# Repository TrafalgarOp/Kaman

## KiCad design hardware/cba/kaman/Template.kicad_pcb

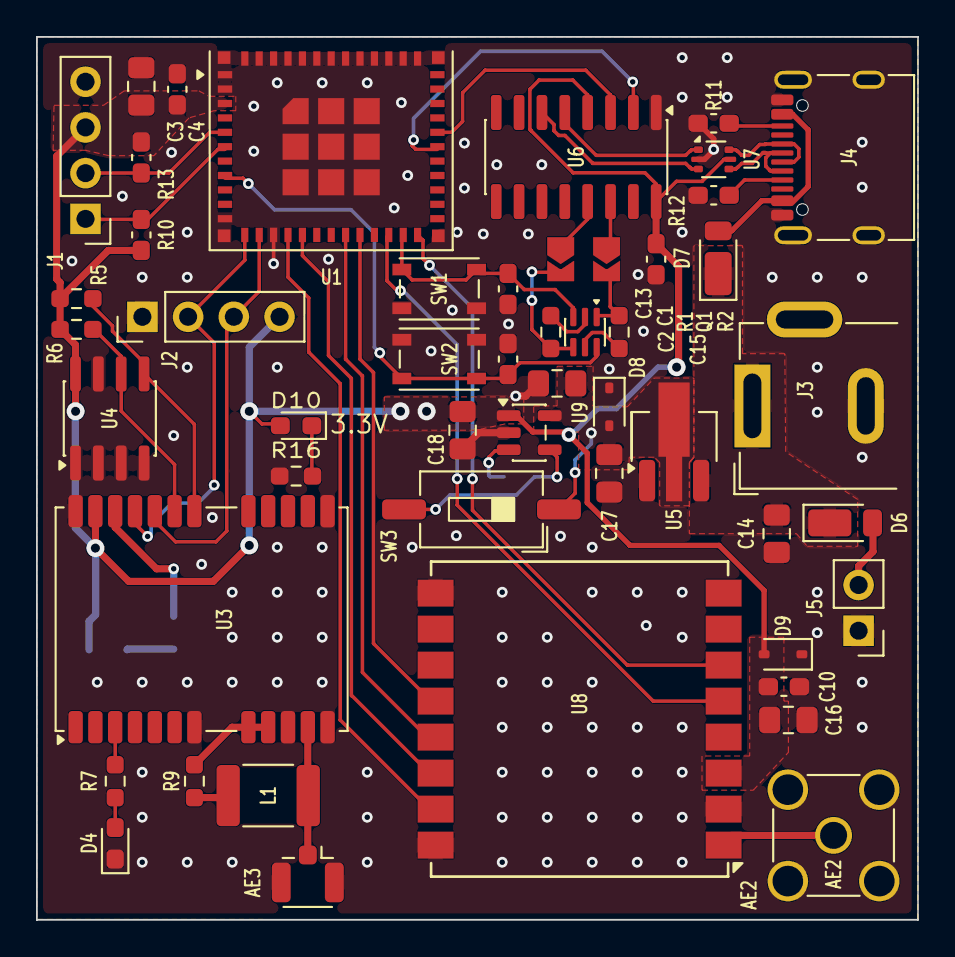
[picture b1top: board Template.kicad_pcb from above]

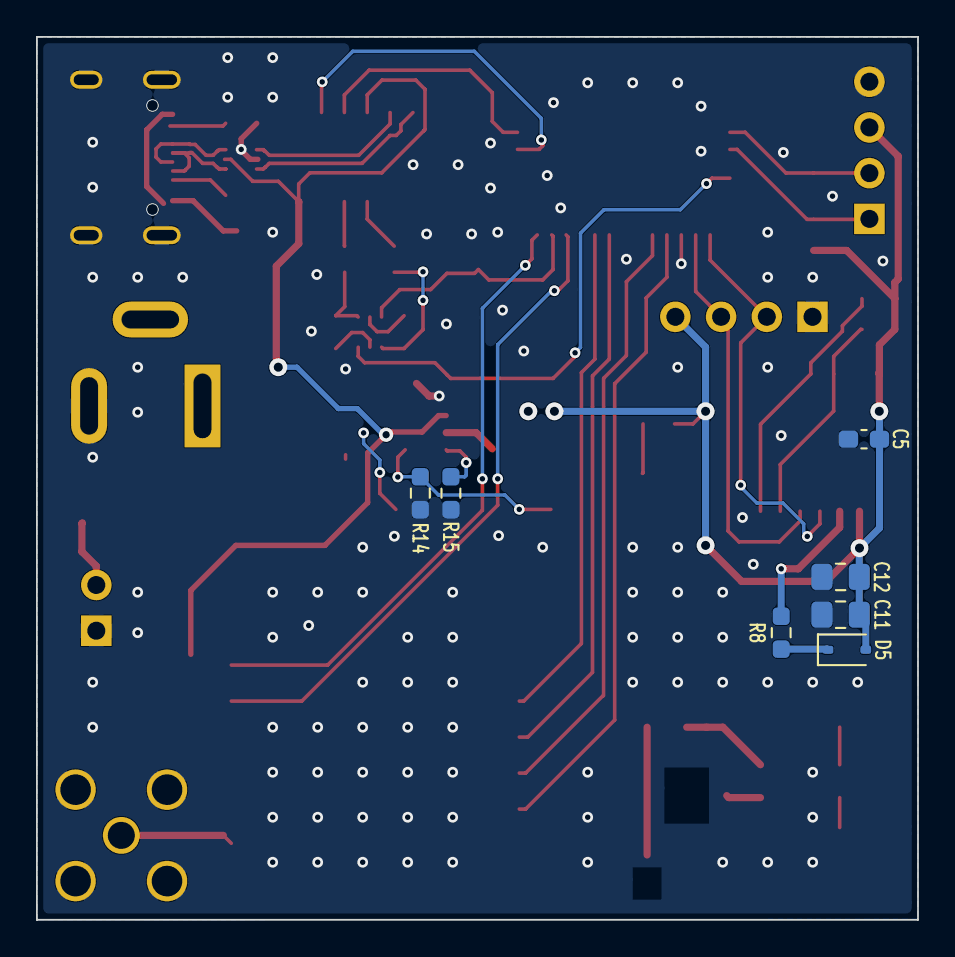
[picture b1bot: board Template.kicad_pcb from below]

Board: 2 copper layers, 48.9 x 49.0 mm, 57 parts (7 on the bottom side), 45 nets.

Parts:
AE2: Antenna_Shield; SMA_Amphenol_132134-11_Vertical
AE3: Antenna_Shield; U.FL_Hirose_U.FL-R-SMT-1_Vertical
C1, C2, C4, C5, C10, C13: 100nF; C_0603_1608Metric_Pad1.08x0.95mm_HandSolder
C3, C14, C15, C16, C17, C18: 10uF; C_0805_2012Metric_Pad1.18x1.45mm_HandSolder
C11, C12: 4.7uF; C_0805_2012Metric_Pad1.18x1.45mm_HandSolder
D4, D10: LED; LED_0603_1608Metric_Pad1.05x0.95mm_HandSolder
D5: 1N5819WT; D_SOD-323
D6, D7: DFLS160-7; D_PowerDI-123
D8: SD05C-01F; D_SOD-323
D9: SD03C-MMD; D_SOD-323
J1, J2: Conn_01x04_Pin; PinHeader_1x04_P2.54mm_Vertical
J3: Barrel_Jack_MountingPin; BarrelJack_GCT_DCJ200-10-A_Horizontal
J4: USB_C_Receptacle_USB2.0_16P; USB_C_Receptacle_G-Switch_GT-USB-7010ASV
J5: Conn_01x02_Socket; PinHeader_1x02_P2.54mm_Vertical
JP1, JP2: SolderJumper_2_Open; SolderJumper-2_P1.3mm_Open_TrianglePad1.0x1.5mm
L1: 27uH; L_1812_4532Metric_Pad1.30x3.40mm_HandSolder
Q1: MMDT5551; SOT-363_SC-70-6
R1, R2: 10K; R_0603_1608Metric_Pad0.98x0.95mm_HandSolder
R5, R6, R7, R8, R14, R16: 1K; R_0603_1608Metric_Pad0.98x0.95mm_HandSolder
R9: 22; R_0603_1608Metric_Pad0.98x0.95mm_HandSolder
R10, R13: 4.7K; C_0603_1608Metric_Pad1.08x0.95mm_HandSolder
R11, R12: 5.1K; C_0603_1608Metric_Pad1.08x0.95mm_HandSolder
R15: 6.8K; R_0603_1608Metric_Pad0.98x0.95mm_HandSolder
SW1, SW2: SW_Push; SW_SPST_PTS810
SW3: SW_DIP_x01; SW_DIP_SPSTx01_Slide_6.7x4.1mm_W8.61mm_P2.54mm_LowProfile
U1: ESP32-C6-MINI-1
U3: NEO-M8N; ublox_NEO
U4: AT24CS64-SSHM; SOIC-8_3.9x4.9mm_P1.27mm
U5: AZ1117-3.3; SOT-89-3_Handsoldering
U6: CH340C; SOIC-16_3.9x9.9mm_P1.27mm
U7: PRTR5V0U2D; SOT-666
U8: Ai-Thinker-Ra-01; Ai-Thinker-Ra-01-LoRa
U9: SY6280AAAC; SOT-23-5

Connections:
+3.3V: C3.1, C4.1, C5.1, C10.1, C11.1, C12.1, C13.1, C16.1, C18.1, D5.2 (A), D9.2 (A2), D10.2 (A), J1.3, J2.4, R5.1, R6.1, R10.1, R13.1, U1.3 (3V3), U3.23 (VCC), U4.8 (VCC), U6.4 (V3), U6.16 (VCC), U7.5 (VBUS), U8.3 (VDD), U9.1 (OUT)
/Project Architecture/IO Port/USB2_N: U6.6 (UD-), U7.3 (I/O2)
/Project Architecture/IO Port/USB2_P: U6.5 (UD+), U7.1 (I/O1)
/Project Architecture/IO Port/USB_N: J4.A7 (D-), J4.B7 (D-), U7.4 (I/O2)
/Project Architecture/IO Port/USB_P: J4.A6 (D+), J4.B6 (D+), U7.6 (I/O1)
/Project Architecture/MCU & GPS/VCC RF: R9.1, U3.8 (~RESET), U3.9 (VCC_RF)
BUSY LoRa: U1.22 (IO8), U8.5 (DIO0)
DIO1 LoRa: U1.24 (IO18), U8.6 (DIO1)
DTR: JP1.1 (A), U6.13 (~DTR)
EN: C2.2, Q1.6 (C1), SW2.2, U1.8 (EN)
GND: AE2.2 (Shield), AE3.2 (Shield), C1.1, C2.1, C3.2, C4.2, C5.2, C10.2, C11.2, C12.2, C13.2, C14.2, C15.2, C16.2, C17.2, C18.2, D4.1 (K), D8.1 (A1), D9.1 (A1), J1.4, J2.1, J3.2, J4.A1 (GND), J4.A12 (GND), J4.B1 (GND), J4.B12 (GND), J4.SH (SHIELD), J5.1, R11.1, R12.1, R14.2, R15.2, R16.1, SW1.1, SW2.1, U1.1 (GND), U1.2 (GND), U1.11 (GND), U1.14 (GND), U1.36 (GND), U1.37 (GND), U1.38 (GND), U1.39 (GND), U1.40 (GND), U1.41 (GND), U1.42 (GND), U1.43 (GND), U1.44 (GND), U1.45 (GND), U1.46 (GND), U1.47 (GND), U1.48 (GND), U1.49 (GND), U1.50 (GND), U1.51 (GND), U1.52 (GND), U1.53 (GND), U3.7 (VDD_USB), U3.10 (GND), U3.12 (GND), U3.13 (GND), U3.24 (GND), U4.1 (A0), U4.2 (A1), U4.3 (A2), U4.4 (GND), U4.7 (WP), U5.1 (GND), U6.1 (GND), U7.2 (GND), U8.2 (GND), U8.9 (GND), U8.16 (GND), U9.2 (GND)
GPIO 9: C1.2, Q1.3 (C2), SW1.2, U1.23 (IO9)
GPS RX: J2.2, U1.12 (IO0), U3.21 (RXD/SPI_MOSI)
GPS TX: J2.3, U1.13 (IO1), U3.20 (TXD/SPI_MISO)
MISO LoRa: U1.16 (IO7), U8.14 (MOSI)
MOSI LoRa: U1.19 (IO14), U8.13 (MISO)
NSS LoRa: U1.15 (IO6), U8.15 (~NSS)
unnamed: AE2.1 (A), U8.1 (ANT)
unnamed: AE3.1 (A), L1.2, U3.11 (RF_IN)
unnamed: D4.2 (A), R7.2
unnamed: D5.1 (K), R8.1
unnamed: D6.2 (A), J5.2
unnamed: D7.2 (A), J4.A4 (VBUS), J4.A9 (VBUS), J4.B4 (VBUS), J4.B9 (VBUS)
unnamed: C15.1, C17.1, D8.2 (A2), SW3.1, U5.2 (VO), U9.5 (IN)
unnamed: D10.1 (K), R16.2
unnamed: J4.A5 (CC1), R12.2
unnamed: J4.B5 (CC2), R11.2
unnamed: JP1.2 (B), Q1.4 (E2), R1.1
unnamed: JP2.2 (B), Q1.1 (E1), R2.1
unnamed: L1.1, R9.2
unnamed: Q1.2 (B1), R1.2
unnamed: Q1.5 (B2), R2.2
unnamed: R6.2, U3.19 (SCL/SPI_CLK), U4.6 (SCL)
unnamed: R5.2, U3.18 (SDA/~SPI_CS), U4.5 (SDA)
unnamed: R7.1, U3.3 (TIMEPULSE)
unnamed: R8.2, U3.22 (V_BCKP)
unnamed: R14.1, SW3.2, U9.4 (EN)
unnamed: R15.1, U9.3 (ISET)
RTS: JP2.1 (A), U6.14 (~RTS)
SCK LoRa: U1.20 (IO15), U8.12 (SCK)
SCL Oled: J1.2, R13.2, U1.5 (IO2)
SDA Oled: J1.1, R10.2, U1.6 (IO3)
UART RX: U1.30 (RXD0), U6.2 (TXD)
UART TX: U1.31 (TXD0), U6.3 (RXD)
VDD: C14.1, D6.1 (K), D7.1 (K), J3.1, U5.3 (VI)
